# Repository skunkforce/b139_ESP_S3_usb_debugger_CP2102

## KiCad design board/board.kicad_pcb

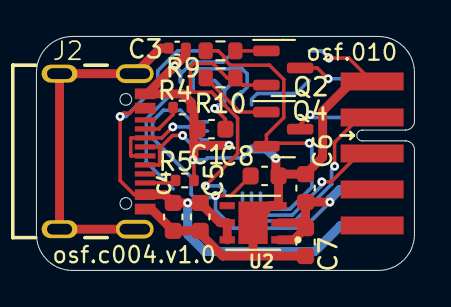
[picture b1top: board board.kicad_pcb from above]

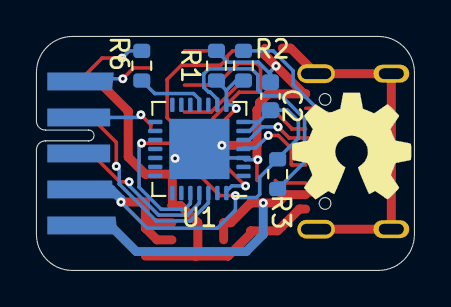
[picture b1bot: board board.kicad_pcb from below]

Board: 2 copper layers, 21.0 x 13.0 mm, 23 parts (7 on the bottom side), 19 nets.

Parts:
C1, C4, C8: 1uF; C_0603_1608Metric
C2, C5, C6, C7: 10uF; C_0603_1608Metric
C3: 100pF; C_0402_1005Metric
J1: 010_UART; on_edge_2x05_host
J2: USB4105-GF-A; GCT_USB4105-GF-A
LOGO1: Logo_Open_Hardware_Small; OSHW-Symbol_6.7x6mm_SilkScreen
Q2, Q4: NXV55UN; SOT-23
R1: 47.5k; R_0603_1608Metric
R2: 22.1k; R_0603_1608Metric
R3: 1k; R_0603_1608Metric
R4, R5: 5.1k; R_0402_1005Metric
R6: 10k; R_0603_1608Metric
R9, R10: 0R; R_0603_1608Metric
U1: CP2102N-Axx-xQFN28; QFN-28-1EP_5x5mm_P0.5mm_EP3.35x3.35mm
U2: LD39200PU33R; SON95P300X300X100-7N

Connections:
+3.3V: C2.1, C6.1, C7.1, C8.1, J1.9 (3.3V), R3.1, U1.6 (VDD), U1.7 (VREGIN), U2.1 (OUT), U2.2 (SENSE)
+5V: C4.1, C5.1, J1.10 (5V), J2.A4/B9 (VBUS), J2.B4/A9 (VBUS), R2.1, U2.5 (EN), U2.6 (IN)
/cp2102/DTR: Q2.2 (S), R10.1, U1.28 (~DTR)
/cp2102/RTS: Q4.2 (S), R9.1, U1.24 (~RTS)
/cp2102/UART_RX: J1.3 (RX), U1.25 (RXD)
/cp2102/USB_DM: J2.A7 (DN1), J2.B7 (DN2), U1.5 (D-)
/cp2102/USB_DP: J2.A6 (DP1), J2.B6 (DP2), U1.4 (D+)
/cp2102/USRT_TX: J1.2 (TX), U1.26 (TXD)
/cp2102/~reset: R3.2, U1.9 (~RST)
GND: C1.2, C2.2, C3.2, C4.2, C5.2, C6.2, C7.2, C8.2, J1.1 (GND), J2.A1/B12 (GND), J2.B1/A12 (GND), R1.2, R4.2, R5.2, R6.2, U1.3 (GND), U1.29 (GND), U2.3 (GND), U2.7 (EXP)
unnamed: C3.1, J2.G1 (SCHIELD), J2.G2 (SCHIELD), J2.G3 (SCHIELD), J2.G4 (SCHIELD)
unnamed: J1.6 (CS/EN), Q2.3 (D)
unnamed: J1.7 (~RESET), Q4.3 (D)
unnamed: J2.A5 (CC1), R4.1
unnamed: J2.B5 (CC2), R5.1
unnamed: Q2.1 (G), R9.2
unnamed: Q4.1 (G), R10.2
unnamed: C1.1, R1.1, R2.2, U1.8 (VBUS)
unnamed: R6.1, U1.11 (~SUSPEND)

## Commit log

2023-06-23 initial
2023-06-23 schemetic finished
2023-06-23 layout finished
